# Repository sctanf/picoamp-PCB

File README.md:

# indexspeakerdacsmol

compact usb-i2s dac using rp2040 and max98360a for powering speakers, like index bmr drivers

* I forgot the silkscreen for usb pins, but they should be clear from below images.
* 0201 components suck to work with.
* intended to use with a usb-c cable, however the CC wire needs 5.1K pull-down to ground which I forgot about

firmware for the device is at https://github.com/sctanf/picoamp-2

pcb|3d|dev-pcb|dev-3d
--|--|--|--
|||

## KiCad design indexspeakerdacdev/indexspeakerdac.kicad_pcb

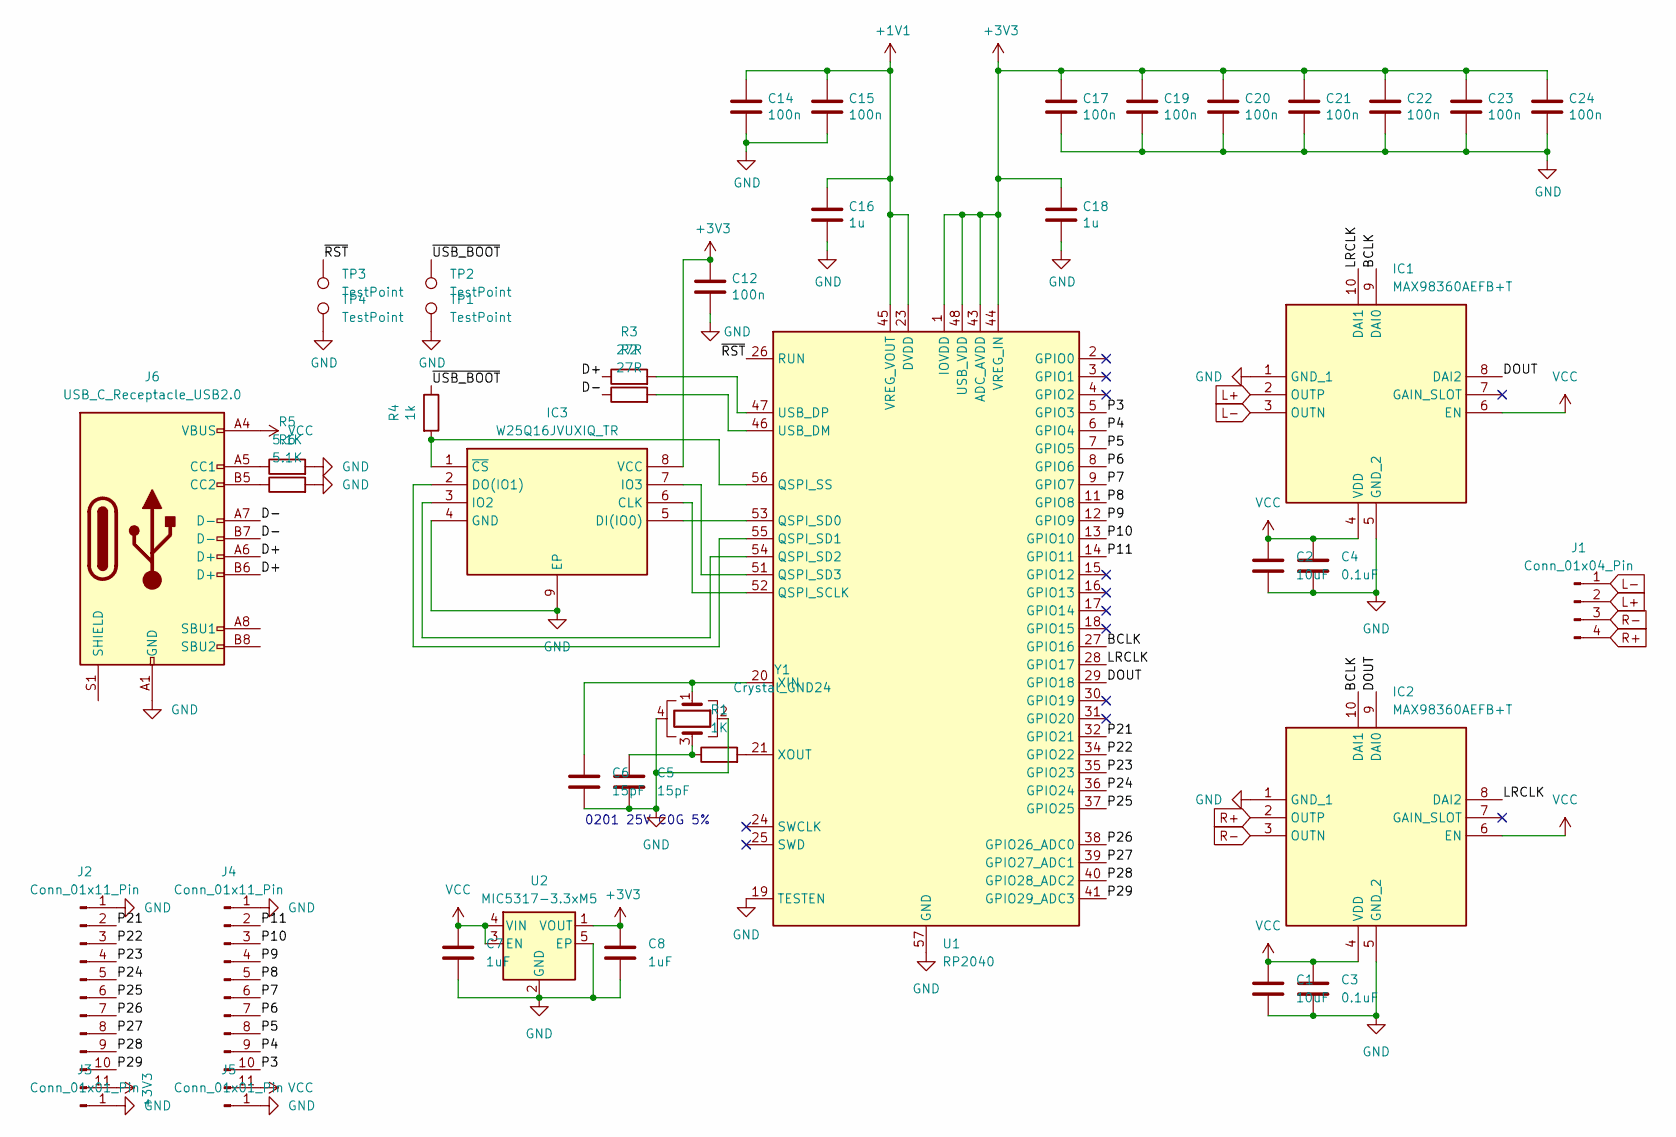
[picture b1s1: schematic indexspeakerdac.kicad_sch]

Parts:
C1, C2: 10uF; C_0603_1608Metric
C3, C4: 0.1uF; C_0402_1005Metric
C5, C6: 15pF; C_0201_0603Metric
C7, C8: 1uF; C_0402_1005Metric
C12, C14, C15, C17, C19, C20, C21, C22, C23, C24: 100n; C_0201_0603Metric
C16, C18: 1u; C_0402_1005Metric
IC1, IC2: MAX98360AEFB+T; MAX98360AEFB; Mouser Part Number 700-MAX98360AEFB+T
IC3: W25Q16JVUXIQ_TR; SON50P300X200X60-9N; Mouser Part Number 454-W25Q16JVUXIQTR
J1: Conn_01x04_Pin; PinHeader_1x04_P2.00mm_Horizontal
J2, J4: Conn_01x11_Pin; PinHeader_1x11_P2.00mm_Vertical
J3, J5: Conn_01x01_Pin; PinHeader_1x01_P2.00mm_Vertical
J6: USB_C_Receptacle_USB2.0
R1: 1K; R_0402_1005Metric
R2, R3: 27R; R_0201_0603Metric
R4: 1k; R_0201_0603Metric
R5, R6: 5.1K; R_0201_0603Metric
TP1, TP2, TP3, TP4: TestPoint; TestPoint_Pad_1.0x1.0mm
U1: RP2040; QFN-56-1EP_7x7mm_P0.4mm_EP3.2x3.2mm
U2: MIC5317-3.3xM5; UDFN-4-1EP_1x1mm_P0.65mm_EP0.48x0.48mm
Y1: Crystal_GND24; Crystal_SMD_3225-4Pin_3.2x2.5mm

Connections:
+1V1: C14.1, C15.1, C16.1, U1.23 (DVDD), U1.45 (VREG_VOUT), U1.50 (DVDD)
+3V3: C8.1, C12.1, C17.1, C18.1, C19.1, C20.1, C21.1, C22.1, C23.1, C24.1, IC3.8 (VCC), J2.11, U1.1 (IOVDD), U1.10 (IOVDD), U1.22 (IOVDD), U1.33 (IOVDD), U1.42 (IOVDD), U1.43 (ADC_AVDD), U1.44 (VREG_IN), U1.48 (USB_VDD), U1.49 (IOVDD), U2.1 (VOUT)
/BCLK: IC1.9 (DAI0), IC2.10 (DAI1), U1.27 (GPIO16)
/D+: J6.A6 (D+), J6.B6 (D+), R3.1
/D-: J6.A7 (D-), J6.B7 (D-), R2.1
/DOUT: IC1.8 (DAI2), IC2.9 (DAI0), U1.29 (GPIO18)
/LRCLK: IC1.10 (DAI1), IC2.8 (DAI2), U1.28 (GPIO17)
/P3: J4.10, U1.5 (GPIO3)
/P4: J4.9, U1.6 (GPIO4)
/P5: J4.8, U1.7 (GPIO5)
/P6: J4.7, U1.8 (GPIO6)
/P7: J4.6, U1.9 (GPIO7)
/P8: J4.5, U1.11 (GPIO8)
/P9: J4.4, U1.12 (GPIO9)
/P10: J4.3, U1.13 (GPIO10)
/P11: J4.2, U1.14 (GPIO11)
/P21: J2.2, U1.32 (GPIO21)
/P22: J2.3, U1.34 (GPIO22)
/P23: J2.4, U1.35 (GPIO23)
/P24: J2.5, U1.36 (GPIO24)
/P25: J2.6, U1.37 (GPIO25)
/P26: J2.7, U1.38 (GPIO26_ADC0)
/P27: J2.8, U1.39 (GPIO27_ADC1)
/P28: J2.9, U1.40 (GPIO28_ADC2)
/P29: J2.10, U1.41 (GPIO29_ADC3)
/~RST: TP3.1, U1.26 (RUN)
/~USB_BOOT: R4.1, TP2.1
GND: C1.2, C2.2, C3.2, C4.2, C5.2, C6.2, C7.2, C8.2, C12.2, C14.2, C15.2, C16.2, C17.2, C18.2, C19.2, C20.2, C21.2, C22.2, C23.2, C24.2, IC1.1 (GND_1), IC1.5 (GND_2), IC2.1 (GND_1), IC2.5 (GND_2), IC3.4 (GND), IC3.9 (EP), J2.1, J3.1, J4.1, J5.1, J6.A1 (GND), J6.A12 (GND), J6.B1 (GND), J6.B12 (GND), R5.2, R6.2, TP1.1, TP4.1, U1.19 (TESTEN), U1.57 (GND), U2.2 (GND), U2.5 (EP), Y1.2, Y1.4
L+: IC1.2 (OUTP), J1.2
L-: IC1.3 (OUTN), J1.1
unnamed: C5.1, R1.1, Y1.3
unnamed: IC3.6 (CLK), U1.52 (QSPI_SCLK)
unnamed: IC3.5 (DI(IO0)), U1.53 (QSPI_SD0)
unnamed: IC3.2 (DO(IO1)), U1.55 (QSPI_SD1)
unnamed: IC3.3 (IO2), U1.54 (QSPI_SD2)
unnamed: IC3.7 (IO3), U1.51 (QSPI_SD3)
unnamed: IC3.1 (~CS), R4.2, U1.56 (QSPI_SS)
unnamed: J6.A5 (CC1), R5.1
unnamed: J6.B5 (CC2), R6.1
unnamed: R2.2, U1.46 (USB_DM)
unnamed: R3.2, U1.47 (USB_DP)
unnamed: C6.1, U1.20 (XIN), Y1.1
unnamed: R1.2, U1.21 (XOUT)
R+: IC2.2 (OUTP), J1.4
R-: IC2.3 (OUTN), J1.3
VCC: C1.1, C2.1, C3.1, C4.1, C7.1, IC1.4 (VDD), IC1.6 (EN), IC2.4 (VDD), IC2.6 (EN), J4.11, J6.A4 (VBUS), J6.A9 (VBUS), J6.B4 (VBUS), J6.B9 (VBUS), U2.3 (EN), U2.4 (VIN)

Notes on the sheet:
0201 25V C0G 5%

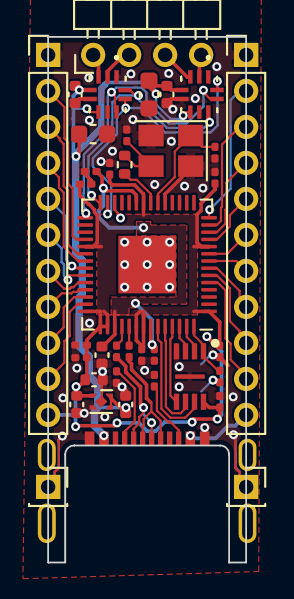
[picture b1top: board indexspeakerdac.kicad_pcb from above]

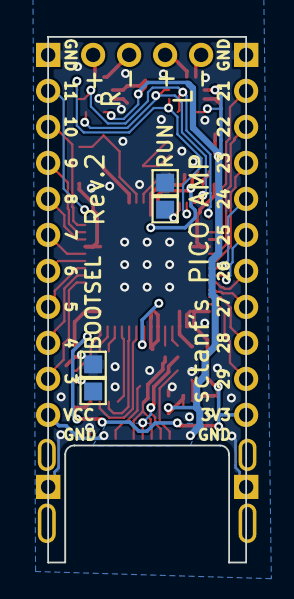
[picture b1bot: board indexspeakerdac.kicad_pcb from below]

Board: 2 copper layers, 11.0 x 29.2 mm, 42 parts (4 on the bottom side), 46 nets.

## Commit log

2024-01-05 add production file
2024-01-05 add rendered images
2024-01-05 add finished images
2024-01-11 replace 3d image
2024-01-16 add rev.2 board
2024-01-19 round connector cutout area
2024-01-20 add bom
2025-08-03 link to new firmware
2025-09-08 add ohl license
2025-09-08 Add LICENSE file for CERN OHL v2
